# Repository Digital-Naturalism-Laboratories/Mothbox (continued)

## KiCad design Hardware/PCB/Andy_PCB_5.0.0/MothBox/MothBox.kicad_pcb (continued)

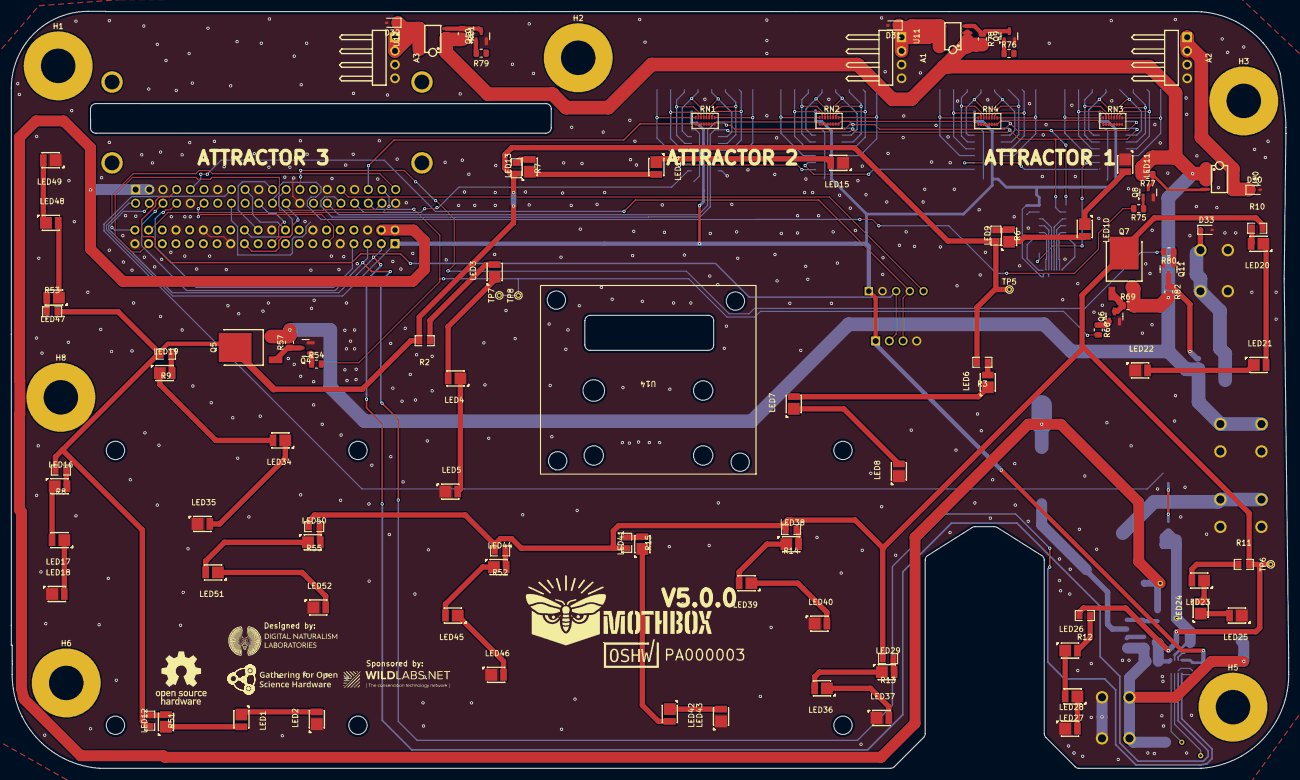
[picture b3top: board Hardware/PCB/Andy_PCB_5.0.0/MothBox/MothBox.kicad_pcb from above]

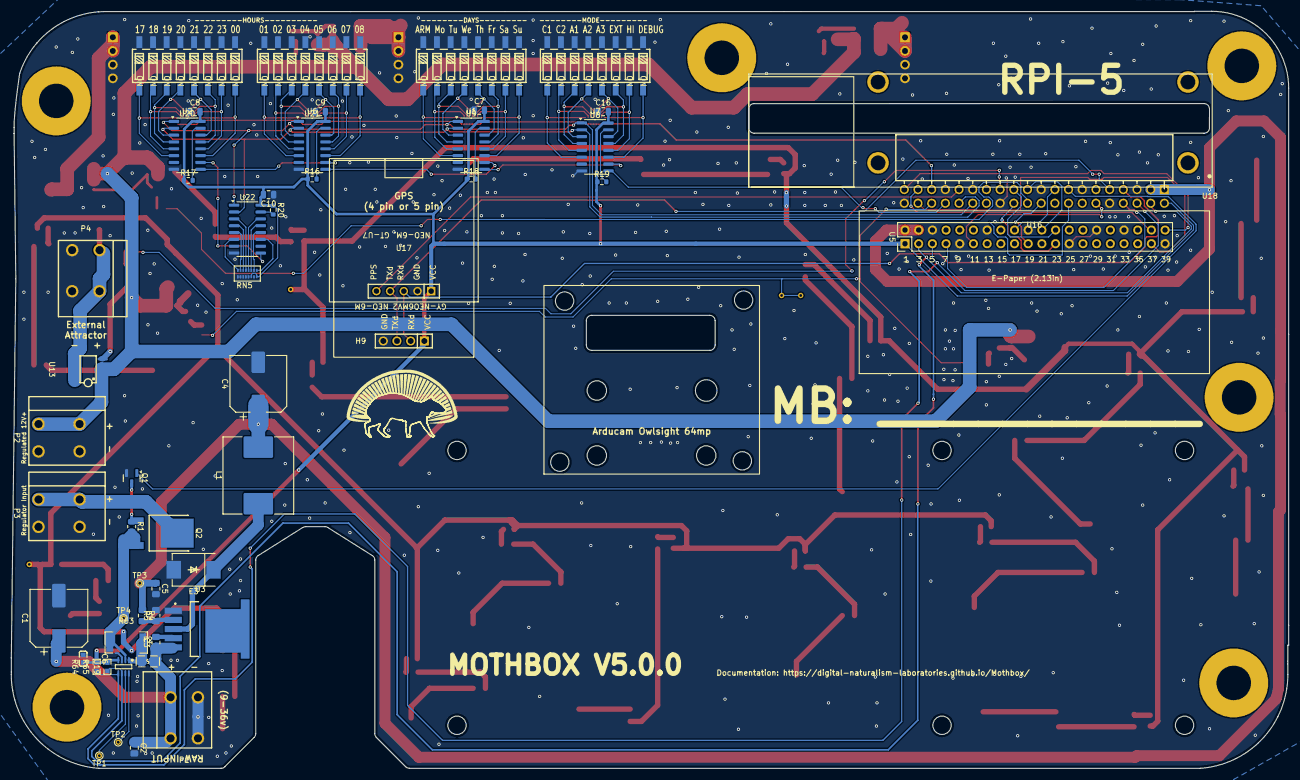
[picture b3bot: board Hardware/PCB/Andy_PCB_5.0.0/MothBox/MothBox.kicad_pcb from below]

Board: 2 copper layers, 237.0 x 140.5 mm, 163 parts (54 on the bottom side), 152 nets.

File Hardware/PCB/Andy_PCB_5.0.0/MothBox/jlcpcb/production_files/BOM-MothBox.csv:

Comment,Designator,Footprint,LCSC,Quantity
3.3K,R5,C_0805_2012Metric_Pad1.18x1.45mm_HandSolder,C114531,1
SUD50P06-15-GE3,"Q2,Q5,Q7",TO-252-3_L6.5-W5.8-P4.58-BL,C141584,3
0.1µF,C6,C0603,C14663,1
Polyfuse,F2,F0805,C22435897,1
0.1/1% (PT2512FK-070R1L),R63,R2512,C23067426,1
FDS4435BZ,"U10,U11,U12,U13",SOIC-8_L5.0-W4.0-P1.27-LS6.0-BL,C23931,4
330uF 50V,C4,CP_Elec_10x10,C2687701,1
GPS 4 pin 2.54-1*4P母,H9,GPS4pin_HDR-TH_4P-P2.54-V-F,C2718488,1
XL-2835UWC-02,"LED1,LED10,LED11,LED12,LED13,LED14,LED15,LED16,LED17,LED18,LED19,LED2,LED20,LED21,LED22,LED23,LED24,LED25,LED26,LED27,LED28,LED29,LED3,LED34,LED35,LED36,LED37,LED38,LED39,LED4,LED40,LED41,LED42,LED43,LED44,LED45,LED46,LED47,LED48,LED49,LED5,LED50,LED51,LED52,LED6,LED7,LED8,LED9",LED-SMD_L3.5-W2.8-RD_1.25T-2PWT,C2843876,48
Female Inv Socket Pi 2.54-2*20,U16,HDR-TH_40P-P2.54-H-F-R2-C20-W8.5,C2897440,1
Raw Input,"P1,P2,P3,P4",CONN-TH_2P-P5.08_DIBO_DB142R-5.08-2P,C2898709,4
FRC0805F30R0TS,"R10,R11,R12,R13,R14,R15,R51,R52,R53,R6,R7,R8,R9",R0805,C2907256,13
10k,"R64,R65",R0603,C2930027,2
FRC0805F30R0TS,"R2,R3,R55",R0805,C2934094,3
0.1uF 50V,"C2,C3,C5",C_0805_2012Metric_Pad1.18x1.45mm_HandSolder,C2976900,3
BC817,"Q1,Q10,Q11,Q4,Q6,Q8,Q9",SOT-23,C39828,7
ESD12VD3B-TP,"D30,D31,D32,D33",D_SOD-323,C435886,4
PZ254R-11-04P,"A1,A2,A3",HDR-TH_4P-P2.54-H-M-W10.4,C492412,3
CD74HC4067M96E4,"U8,U9",SOIC-24_L15.4-W7.5-P1.27-LS10.3-BL,C496123,2
0.1uF,"C16,C17",C_0805_2012Metric,C49678,2
5A 47uH,L1,L_Chilisin_BMRG00131360,C497913,1
GPs 5 pin PM2.54-1*5,U17,GPS5pin_HDR-TH_5P-P2.54-V-F,C5116488,1
XL4015E1,U3,TO-263-5_L10.2-W8.9-P1.70-TL,C51661,1
RASPBERRY_PI_5,U5,EPAPER_PinHeader_2x20_P2.54mm_Vertical,C5224014,1
Days,"U1,U2,U6,U7",SW-SMD_SMXS-08K-TP,C5439767,4
SK54C,E3,SMC_L6.9-W5.9-LS8.0-RD,C5449119,1
10k,"R1,R4,R57,R69,R77,R78,R81,R82",R_0805_2012Metric,C84376,8
INA219BIDCNT,U19,SOT-23-8_L3.0-W1.7-P0.65-LS2.8-BR,C87469,1
470uF 50V,C1,CP_Elec_10x12.5,C90272,1
1k,"R54,R66,R75,R76,R79,R80",R_0805_2012Metric,C95781,6
RASPBERRY_PI_4B_4GB,U18,MODULE_RASPBERRY_PI_4B_4GB_Sideways,,1
~,B1,Talentcell,,1

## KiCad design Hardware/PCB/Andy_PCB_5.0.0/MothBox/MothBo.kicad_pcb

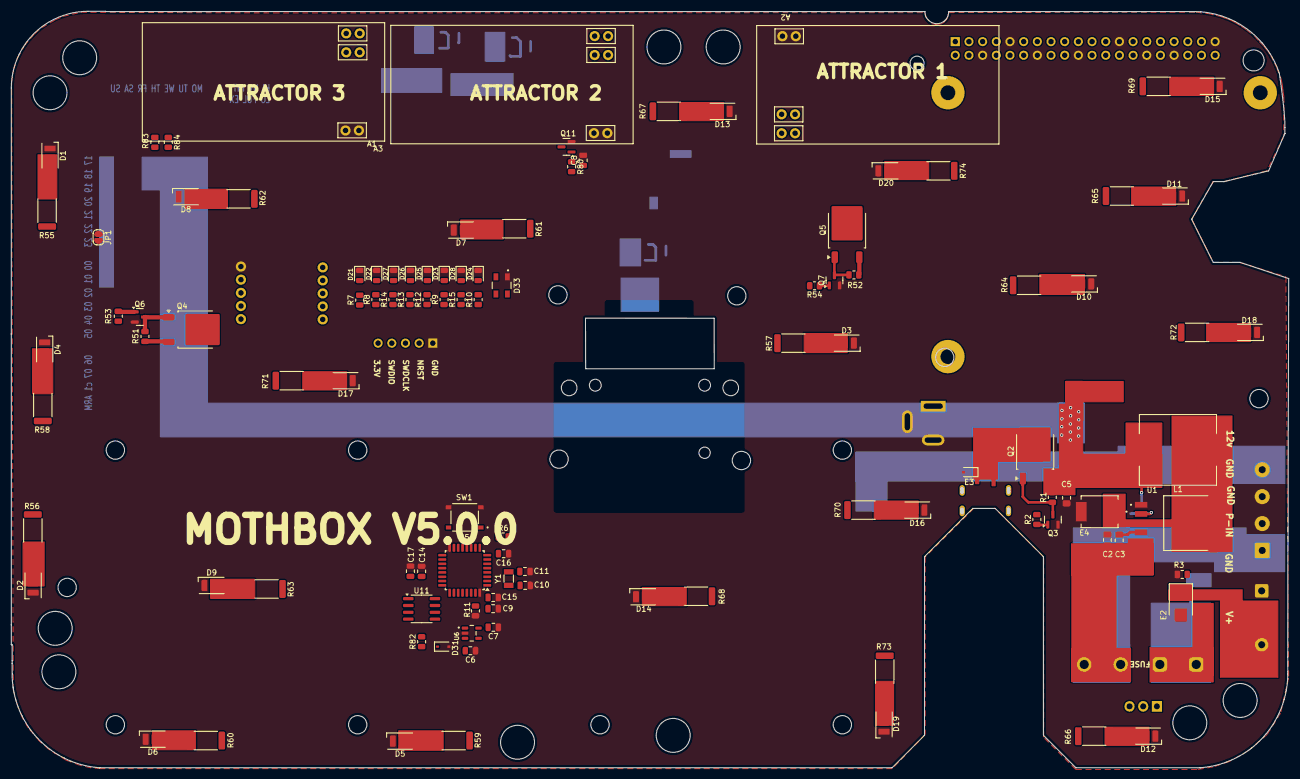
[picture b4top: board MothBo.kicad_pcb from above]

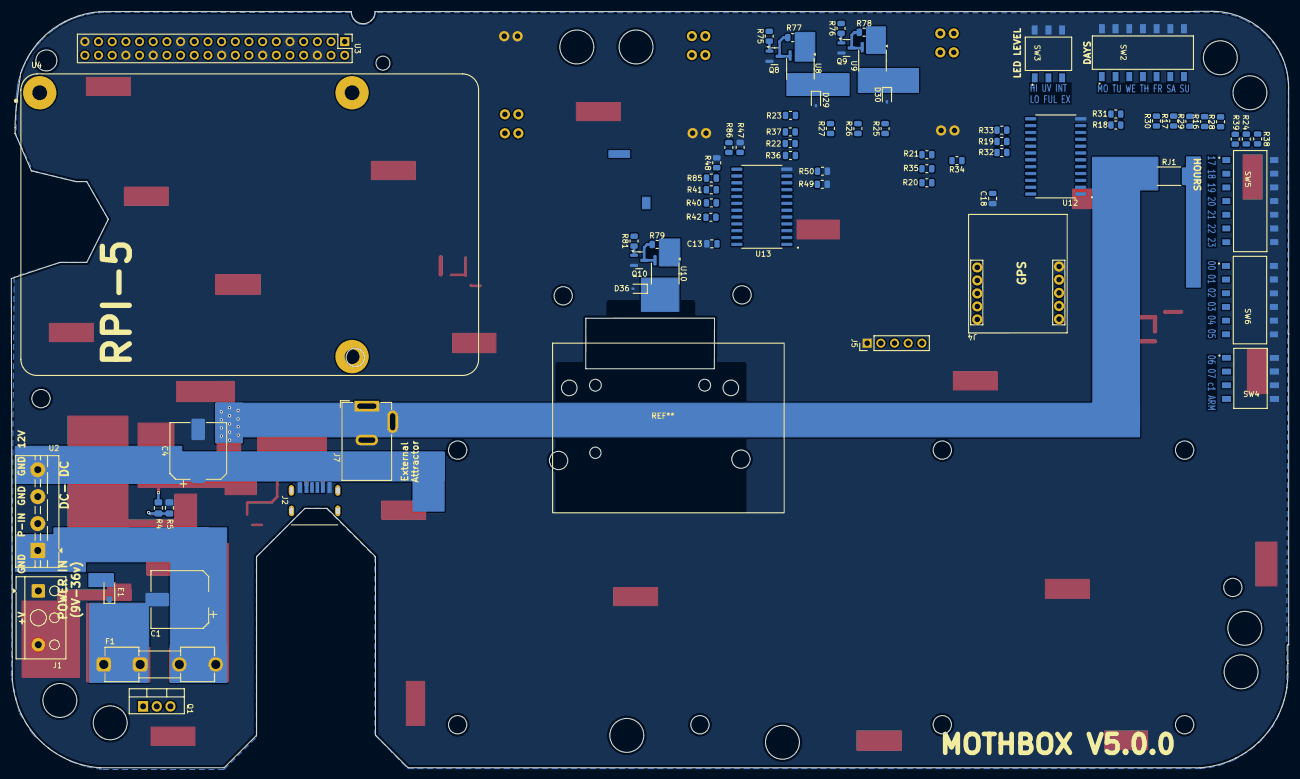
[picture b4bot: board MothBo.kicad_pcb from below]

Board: 2 copper layers, 237.2 x 140.5 mm, 178 parts (73 on the bottom side), 119 nets.

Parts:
A1, A2, A3: Attractor; attractor
C1: 470uF 50V; CP_Elec_10x12.5
C2, C3, C5: 0.1uF 50V; C_0805_2012Metric_Pad1.18x1.45mm_HandSolder
C4: 330uF 50V; CP_Elec_10x10
C6, C7, C17: 1uF; C_0805_2012Metric
C8: 100nF; C_0805_2012Metric
C9, C13, C14, C15, C16, C18: 0.1uF; C_0805_2012Metric
C10, C11: 12pF; C_0805_2012Metric
D1, D2, D3, D4, D5, D6, D7, D8, D9, D10, D11, D12, D13, D14, D15, D16, D17, D18, D19, D20: LED; LED_Everlight-SMD3528_3.5x2.8mm_67-21ST
D21, D22, D23, D24, D25, D26, D27, D28: LED; LED_0805_2012Metric
D29, D30, D31, D36: ESD12VD3B-TP; D_SOD-323
D33: IN-PI33TBTPRPGPB; LED_IN-PI33TBTPRPGPB
E1: BZT52Bxx; D_SOD-123F
E2: SMBJ36A; D_SMB
E3: ESD5V0D3B; D_SOD-323
E4: SK54C; DIO_SK54C
F1: 7A Fuse; Fuseholder_Clip-5x20mm_Eaton_1A5601-01_Inline_P20.80x6.76mm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
J1: Screw_Terminal_01x02; TerminalBlock_RND_205-00023_1x02_P10.00mm_Horizontal
J2: TYPE-C-31-M-17; TYPEC31M17
J4: GPS Header; Untitled
J5: Conn_01x05_Pin; PinHeader_1x05_P2.54mm_Vertical
J7: DC Power Jack; BarrelJack_GCT_DCJ200-10-A_Horizontal
JP1: SolderJumper_2_Open; SolderJumper-2_P1.3mm_Open_RoundedPad1.0x1.5mm
L1: 5A 47uH; L_Chilisin_BMRG00131360
Q1: IRF9540N; TO-220-3_Vertical
Q2, Q4, Q5: TJ10S04M3L,LXHQ; TO-252-2
Q3, Q6, Q7, Q8, Q9, Q10, Q11: BC817; SOT-23
R1, R3, R16, R17, R18, R19, R20, R21, R22, R23, R24, R25, R26, R27, R28, R29, R30, R31, R32, R33, R34, R35, R36, R37, R38, R39, R40, R41, R42, R51, R52, R77, R78, R79, R82: 10k; R_0805_2012Metric
R2, R7, R8, R9, R10, R12, R13, R14, R15, R53, R54, R75, R76, R80, R81: 1k; R_0805_2012Metric
R4: 10K; C_0805_2012Metric_Pad1.18x1.45mm_HandSolder
R5: 3.3K; C_0805_2012Metric_Pad1.18x1.45mm_HandSolder
R6, R11: 10K; R_0805_2012Metric
R47, R48, R49, R50, R83, R84, R85, R86: DNP; R_0805_2012Metric
R55, R56, R57, R58, R59, R60, R61, R62, R63, R64, R65, R66, R67, R68, R69, R70, R71, R72, R73, R74: 170R; R_2512_6332Metric
RJ1: 0R; R_2512_6332Metric
SW1: SW_Push; SW_TS-1187A-B-A-B
SW2: Days; SW_DS04-254-2-07BK-SMT
SW3: Power; SW_DS04-254-2-03BK-SMT
SW4: seq tog; SW_DS04-254-2-04BK-SMT
SW5: Hours; SW_DS04-254-2-07BK-SMT
SW6: Hours; SW_DS04-254-2-06BK-SMT
U1: XL4015; CONV_XL4015
U2: 9V-36V to 12V 5A 60W; TerminalBlock_MaiXu_MX126-5.0-04P_1x04_P5.00mm
U3: RASPBERRY_PI_5; PinHeader_2x20_P2.54mm_Vertical
U4: RASPBERRY_PI_4B_4GB; MODULE_RASPBERRY_PI_4B_4GB
U5: STM32L031K6Tx; LQFP-32_7x7mm_P0.8mm
U6: TLV75733PDBVR; SOT95P280X145-5N
U8, U9, U10, U11: IRF9335TRPBF; SOIC-8_3.9x4.9mm_P1.27mm
U12, U13: CD74HC4067M96E4; SOIC127P1030X265-24N
Y1: 32.768kHz; Crystal_SMD_3215-2Pin_3.2x1.5mm

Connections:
+3.3V: C7.2, C9.2, C13.2, C14.2, C15.2, C16.2, C17.2, C18.2, D33.3 (VDD), J4.VCC, J5.5, R6.1, R16.1, R17.1, R18.1, R19.1, R20.1, R21.1, R22.1, R23.1, R24.1, R25.1, R26.1, R27.1, R28.1, R29.1, R30.1, R31.1, R32.1, R33.1, R34.1, R35.1, R36.1, R37.1, R38.1, R39.1, R40.1, R41.1, R42.1, R83.1, R84.1, R85.1, R86.1, U3.1 (3V3), U3.17 (3V3), U5.1 (VDD), U5.5 (VDDA), U5.17 (VDD), U6.5 (OUT), U12.24 (VCC), U13.24 (VCC)
+5V: C4.1, C5.1, C6.2, L1.2, Q2.3 (S), R1.2, R4.1, RJ1.1, U6.1 (IN), U6.3 (EN)
+12V: Q4.3 (S), Q5.3 (S), R51.2, R52.2, R77.2, R78.2, R79.2, R82.2, U2.4 (Vout+), U8.1 (S), U8.2 (S), U8.3 (S), U9.1 (S), U9.2 (S), U9.3 (S), U10.1 (S), U10.2 (S), U10.3 (S), U11.1 (S), U11.2 (S), U11.3 (S)
/GPS+Switches/Armed/Disarmed: R21.2, SW4.1A, U12.23 (I8)
/GPS+Switches/Fri: R30.2, SW2.3A, U12.4 (I5)
/GPS+Switches/Hour_1: R36.2, SW5.7A, U13.9 (I0)
/GPS+Switches/Hour_2: R22.2, SW5.6A, U13.8 (I1)
/GPS+Switches/Hour_3: R37.2, SW5.5A, U13.7 (I2)
/GPS+Switches/Hour_4: R23.2, SW5.4A, U13.6 (I3)
/GPS+Switches/Hour_5: R38.2, SW5.3A, U13.5 (I4)
/GPS+Switches/Hour_6: R24.2, SW5.2A, U13.4 (I5)
/GPS+Switches/Hour_7: R39.2, SW5.1A, U13.3 (I6)
/GPS+Switches/Hour_8: R40.2, SW6.6A, U13.18 (I13)
/GPS+Switches/Hour_9: R25.2, SW6.5A, U13.17 (I14)
/GPS+Switches/Hour_10: R41.2, SW6.4A, U13.16 (I15)
/GPS+Switches/Hour_11: R26.2, SW6.3A, U13.19 (I12)
/GPS+Switches/Hour_12: R42.2, SW6.2A, U13.20 (I11)
/GPS+Switches/Hour_13: R27.2, SW6.1A, U13.21 (I10)
/GPS+Switches/Max_PW: R33.2, SW3.1A, U12.16 (I15)
/GPS+Switches/Med_PW: R19.2, SW3.2A, U12.17 (I14)
/GPS+Switches/Min_PW: R32.2, SW3.3A, U12.18 (I13)
/GPS+Switches/Mon: R28.2, SW2.7A, U12.7 (I2)
/GPS+Switches/Sat: R18.2, SW2.2A, U12.5 (I4)
/GPS+Switches/Seq_1: R34.2, SW4.4A, U12.20 (I11)
/GPS+Switches/Seq_2: R20.2, SW4.3A, U12.21 (I10)
/GPS+Switches/Seq_3: R35.2, SW4.2A, U12.22 (I9)
/GPS+Switches/Sun: R31.2, SW2.1A, U12.6 (I3)
/GPS+Switches/Thur: R17.2, SW2.4A, U12.3 (I6)
/GPS+Switches/Tue: R16.2, SW2.6A, U12.8 (I1)
/GPS+Switches/Wed: R29.2, SW2.5A, U12.9 (I0)
/Photo LED's/+12V_L_LED: Q4.1 (D), R55.1, R56.1, R57.1, R58.1, R59.1, R60.1, R61.1, R62.1, R63.1, R64.1
/Photo LED's/+12V_R_LED: Q5.1 (D), R65.1, R66.1, R67.1, R68.1, R69.1, R70.1, R71.1, R72.1, R73.1, R74.1
/Power/FB: R4.2, R5.1, U1.2 (FB)
/Power/PWR_IN: C1.1, C2.1, C3.1, F1.2, U1.5 (VIN), U2.1 (Vin+)
/Power/VBUS: E3.1 (K), J2.A9 (VBUS_1), J2.B9 (VBUS_2), Q2.1 (D)
/RPI5+MCU/BOOT0: R11.1, U5.31 (BOOT0)
/RPI5+MCU/NRST: C8.1, J5.2, R6.2, SW1.A, SW1.B, U5.4 (NRST)
/RPI5+MCU/OSC_IN: C10.2, U5.2 (PC14), Y1.2
/RPI5+MCU/OSC_OUT: C11.2, U5.3 (PC15), Y1.1
/RPI5+MCU/PA2: R9.1, U5.8 (PA2)
/RPI5+MCU/PA3: R10.1, U5.9 (PA3)
/RPI5+MCU/PA4: R12.1, U5.10 (PA4)
/RPI5+MCU/PA5: R13.1, U5.11 (PA5)
/RPI5+MCU/PA6: R14.1, U5.12 (PA6)
/RPI5+MCU/PA7: R15.1, U5.13 (PA7)
/RPI5+MCU/PA8: R7.1, U5.18 (PA8)
/RPI5+MCU/PA11: R8.1, U5.21 (PA11)
/RPI5+MCU/PA12: D33.2 (DIN), U5.22 (PA12)
/RPI5+MCU/STM_RX: U3.10 (GPIO15/RXD0), U5.19 (PA9)
/RPI5+MCU/STM_TX: U3.8 (GPIO14/TXD0), U5.20 (PA10)
/RPI5+MCU/SWDCLK: J5.3, U5.24 (PA14)
/RPI5+MCU/SWDIO: J5.4, U5.23 (PA13)
/RPI5+MCU/Save for eink: U3.11 (GPIO17/GPIO_GEN0), U3.18 (GPIO24/GPIO_GEN5), U3.19 (GPIO10/SPI_MOSI), U3.22 (GPIO25/GPIO_GEN6), U3.23 (GPIO11/SPI_SCLK), U3.24 (GPIO8/~SPI_CE0)
/UV LED PCB/+12V_PCB1: A2.3 (VCC), A2.4 (VCC), D29.1 (K), U8.5 (D), U8.6 (D), U8.7 (D), U8.8 (D)
/UV LED PCB/+12V_PCB2: A1.3 (VCC), A1.4 (VCC), D31.1 (K), U11.5 (D), U11.6 (D), U11.7 (D), U11.8 (D)
/UV LED PCB/+12V_PCB3: A3.3 (VCC), A3.4 (VCC), D30.1 (K), U9.5 (D), U9.6 (D), U9.7 (D), U9.8 (D)
/UV LED PCB/+12V_PCB4: D36.1 (K), J7.1, U10.5 (D), U10.6 (D), U10.7 (D), U10.8 (D)
COM_I/O: U3.36 (GPIO16), U12.1 (COM_I/O), U13.1 (COM_I/O)
EN_MUX1: JP1.1 (A), U3.16 (GPIO23/GPIO_GEN4), U12.15 (~E)
EN_MUX2: JP1.2 (B), U3.29 (GPIO5), U13.15 (~E)
GND: A1.5 (GND), A1.6 (GND), A2.5 (GND), A2.6 (GND), A3.5 (GND), A3.6 (GND), C1.2, C2.2, C4.2, C5.2, C6.1, C7.1, C8.2, C9.1, C10.1, C11.1, C13.1, C14.1, C15.1, C16.1, C17.1, C18.1, D1.1 (K), D2.1 (K), D3.1 (K), D4.1 (K), D5.1 (K), D6.1 (K), D7.1 (K), D8.1 (K), D9.1 (K), D10.1 (K), D11.1 (K), D12.1 (K), D13.1 (K), D14.1 (K), D15.1 (K), D16.1 (K), D17.1 (K), D18.1 (K), D19.1 (K), D20.1 (K), D21.1 (K), D22.1 (K), D23.1 (K), D24.1 (K), D25.1 (K), D26.1 (K), D27.1 (K), D28.1 (K), D29.2 (A), D30.2 (A), D31.2 (A), D33.1 (GND), D36.2 (A), E2.2 (A), E3.2 (A), E4.A, J1.1, J2.A12 (GND_1), J2.B12 (GND_2), J4.GND, J5.1, J7.2, J7.3 (MountPin), Q3.2 (E), Q6.2 (E), Q7.2 (E), Q8.2 (E), Q9.2 (E), Q10.2 (E), Q11.2 (E), R3.1, R5.2, R11.2, R47.2, R48.2, R49.2, R50.2, SW1.C, SW1.D, SW2.1B, SW2.2B, SW2.3B, SW2.4B, SW2.5B, SW2.6B, SW2.7B, SW3.1B, SW3.2B, SW3.3B, SW4.1B, SW4.2B, SW4.3B, SW4.4B, SW5.1B, SW5.2B, SW5.3B, SW5.4B, SW5.5B, SW5.6B, SW5.7B, SW6.1B, SW6.2B, SW6.3B, SW6.4B, SW6.5B, SW6.6B, U1.1 (GND), U2.2 (Vin-), U2.3 (Vout-), U3.6 (GND), U3.9 (GND), U3.14 (GND), U3.20 (GND), U3.25 (GND), U3.30 (GND), U3.34 (GND), U3.39 (GND), U5.16 (VSS), U5.32 (VSS), U6.2 (GND), U12.12 (GND), U13.12 (GND)
GPS_SCL: J4.SCL, U3.5 (GPIO3/SCL1)
GPS_SDA: J4.SDA, U3.3 (GPIO2/SDA1)
L_LED_CTRL: R53.2, R54.2, U3.31 (GPIO6)
unnamed: D1.2 (A), R55.2
unnamed: D2.2 (A), R56.2
unnamed: D3.2 (A), R57.2
unnamed: D4.2 (A), R58.2
unnamed: D5.2 (A), R59.2
unnamed: D6.2 (A), R60.2
unnamed: D7.2 (A), R61.2
unnamed: D8.2 (A), R62.2
unnamed: D9.2 (A), R63.2
unnamed: D10.2 (A), R64.2
unnamed: D11.2 (A), R65.2
unnamed: D12.2 (A), R66.2
unnamed: D13.2 (A), R67.2
unnamed: D14.2 (A), R68.2
unnamed: D15.2 (A), R69.2
unnamed: D16.2 (A), R70.2
unnamed: D17.2 (A), R71.2
unnamed: D18.2 (A), R72.2
unnamed: D19.2 (A), R73.2
unnamed: D20.2 (A), R74.2
unnamed: D21.2 (A), R7.2
unnamed: D22.2 (A), R8.2
unnamed: D23.2 (A), R9.2
unnamed: D24.2 (A), R10.2
unnamed: D25.2 (A), R12.2
unnamed: D26.2 (A), R13.2
unnamed: D27.2 (A), R14.2
unnamed: D28.2 (A), R15.2
unnamed: E1.2 (A), Q1.1 (G), R3.2
unnamed: E1.1 (K), F1.1, Q1.3 (S)
unnamed: E2.1 (K), J1.2, Q1.2 (D)
unnamed: E4.C, L1.1, U1.3 (SW), U1.3.1 (SW)
unnamed: Q2.2 (G), Q3.3 (C), R1.1
unnamed: Q3.1 (B), R2.1
unnamed: Q4.2 (G), Q6.3 (C), R51.1
unnamed: Q5.2 (G), Q7.3 (C), R52.1
unnamed: Q6.1 (B), R53.1
unnamed: Q7.1 (B), R54.1
unnamed: Q8.1 (B), R75.1
unnamed: Q8.3 (C), R77.1, U8.4 (G)
unnamed: Q9.1 (B), R76.1
unnamed: Q9.3 (C), R78.1, U9.4 (G)
unnamed: Q10.1 (B), R81.1
unnamed: Q10.3 (C), R79.1, U10.4 (G)
unnamed: Q11.1 (B), R80.1
unnamed: Q11.3 (C), R82.1, U11.4 (G)
unnamed: RJ1.2, U3.2 (5V), U3.4 (5V)
unnamed: C3.2, U1.4 (VC)
RPI_CTRL: R2.2, U3.35 (GPIO19)
S0_MUX: R50.1, R83.2, U3.33 (GPIO13), U12.10 (S0), U13.10 (S0)
S1_MUX: R49.1, R84.2, U3.13 (GPIO27/GPIO_GEN2), U12.11 (S1), U13.11 (S1)
S2_MUX: R48.1, R85.2, U3.12 (GPIO18/GPIO_GEN1), U12.14 (S2), U13.14 (S2)
S3_MUX: R47.1, R86.2, U3.15 (GPIO22/GPIO_GEN3), U12.13 (S3), U13.13 (S3)
UV1_CTRL: R75.2, R76.2, R80.2, U3.21 (GPIO9/SPI_MISO)
UV4_EX_CTRL: R81.2, U3.26 (GPIO7/~SPI_CE1)

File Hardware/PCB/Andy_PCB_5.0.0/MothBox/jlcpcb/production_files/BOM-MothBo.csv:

Comment,Designator,Footprint,LCSC,Quantity
3.3K,R5,C_0805_2012Metric_Pad1.18x1.45mm_HandSolder,C114531,1
"TJ10S04M3L,LXHQ","Q2,Q4,Q5",TO-252-2,C115837,3
12pF,"C10,C11",C_0805_2012Metric,C1792,2
Days,"SW2,SW5",SW_DS04-254-2-07BK-SMT,C18198129,2
IRF9335TRPBF,"U10,U11,U8,U9",SOIC-8_3.9x4.9mm_P1.27mm,C23931,4
IRF9540N,Q1,TO-220-3_Vertical,C2575,1
330uF 50V,C4,CP_Elec_10x10,C2687701,1
1uF,"C17,C6,C7",C_0805_2012Metric,C28323,3
TYPE-C-31-M-17,J2,TYPEC31M17,C283540,1
SMBJ36A,E2,D_SMB,C2848704,1
170R,"R55,R56,R57,R58,R59,R60,R61,R62,R63,R64,R65,R66,R67,R68,R69,R70,R71,R72,R73,R74,RJ1",R_2512_6332Metric,C2934094,21
0.1uF 50V,"C2,C3,C5",C_0805_2012Metric_Pad1.18x1.45mm_HandSolder,C2976900,3
SW_Push,SW1,SW_TS-1187A-B-A-B,C318884,1
Sequence+Toggle,SW4,SW_DS04-254-2-04BK-SMT,C319038,1
Power,SW3,SW_DS04-254-2-03BK-SMT,C319040,1
DC Power Jack,J7,BarrelJack_GCT_DCJ200-10-A_Horizontal,C319099,1
BZT52Bxx,E1,D_SOD-123F,C362312,1
LED,"D1,D10,D11,D12,D13,D14,D15,D16,D17,D18,D19,D2,D20,D3,D4,D5,D6,D7,D8,D9",LED_Everlight-SMD3528_3.5x2.8mm_67-21ST,C385305,20
BC817,"Q10,Q11,Q3,Q6,Q7,Q8,Q9",SOT-23,C39828,7
9V-36V to 12V 5A 60W,U2,TerminalBlock_MaiXu_MX126-5.0-04P_1x04_P5.00mm,C424682,1
ESD12VD3B-TP,"D29,D30,D31,D36",D_SOD-323,C435886,4
ESD5V0D3B,E3,D_SOD-323,C484322,1
TLV75733PDBVR,U6,SOT95P280X145-5N,C485517,1
CD74HC4067M96E4,"U12,U13",SOIC127P1030X265-24N,C496123,2
Attractor,"A1,A2,A3",attractor,C49661,3
0.1uF,"C13,C14,C15,C16,C18,C8,C9",C_0805_2012Metric,C49678,7
5A 47uH,L1,L_Chilisin_BMRG00131360,C497913,1
XL4015,U1,CONV_XL4015,C51661,1
Screw_Terminal_01x02,J1,TerminalBlock_RND_205-00023_1x02_P10.00mm_Horizontal,C5168775,1
IN-PI33TBTPRPGPB,D33,LED_IN-PI33TBTPRPGPB,C527089,1
7A Fuse,F1,Fuseholder_Clip-5x20mm_Eaton_1A5601-01_Inline_P20.80x6.76mm_D1.70mm_Horizontal,C5381734,1
SK54C,E4,DIO_SK54C,C5449119,1
LED,"D21,D22,D23,D24,D25,D26,D27,D28",LED_0805_2012Metric,C5875740,8
GPS Header,"J4,J5",Untitled,C6332198,2
10k,"R1,R11,R16,R17,R18,R19,R20,R21,R22,R23,R24,R25,R26,R27,R28,R29,R3,R30,R31,R32,R33,R34,R35,R36,R37,R38,R39,R4,R40,R41,R42,R51,R52,R6,R77,R78,R79,R82",R_0805_2012Metric,C84376,38
Hours,SW6,SW_DS04-254-2-06BK-SMT,C880354,1
470uF 50V,C1,CP_Elec_10x12.5,C90272,1
STM32L031K6Tx,U5,LQFP-32_7x7mm_P0.8mm,C94085,1
1k,"R10,R12,R13,R14,R15,R2,R53,R54,R7,R75,R76,R8,R80,R81,R9",R_0805_2012Metric,C95781,15
32.768kHz,Y1,Crystal_SMD_3215-2Pin_3.2x1.5mm,C99010,1
DNP,,R_0805_2012Metric,,0
DNP,,R_0805_2012Metric,,0
DNP,,R_0805_2012Metric,,0
DNP,,R_0805_2012Metric,,0
DNP,,R_0805_2012Metric,,0
DNP,,R_0805_2012Metric,,0
DNP,,R_0805_2012Metric,,0
DNP,,R_0805_2012Metric,,0

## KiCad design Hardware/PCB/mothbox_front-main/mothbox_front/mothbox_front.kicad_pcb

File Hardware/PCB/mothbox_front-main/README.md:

# mothbox_front

Design a mainboard for the MothBox

# TODO
Todo list mostly built off the [list of upcoming features for the Mothbox](https://digital-naturalism-laboratories.github.io/Mothbox/docs/about/upcoming/).

## Circuit Designs

### Photo LEDs (Point person Moritz)
These are the white, distributed LEDs that evenly light up the target area for even photography.

- place 12V UV-light / visible light attractor LED boards
- design white light <--> PI interface
- design led drivers: single constant current driver for UV and Flashlight, Relays to switch between both options, part: LDH-25-350
- place white LEDs and drivers

### Attractor LEDs (Point person Moritz)
- Design circuitry to toggle high power output to the attractor LED ports

### Power Regulation
Ideally this PCB should be able to accept a range of power. A [common power regulator that costs around $15](https://www.amazon.com/dp/B0B6VK8BPN?ref=ppx_yo2ov_dt_b_fed_asin_title&th=1) takes *9-36v* and regulates this to an even 12V at 5amps. It would be nice if we could build this into the board, though it could optionally be purchased as is and the board just made to use 12V.

- Design regulator circuit
- design connector (ideally standard barrel jack connector, or pair of + and - plugs)

### Power Management
- Integrated power monitoring (e.g. integrate something like the Adafruit 4226 INA260)
- Display Charge State

### Physical Programming Interface
The scientists often have a hard time programming features of the Mothbox. If possible, as many of these variables a user needs to set should be available as some kind of physical switch or toggle. 

Ideally these switches should be "soft switches" that just change a state on a pin the Pi can read and the internal software can perform the necessary functions. There are likely too many variables to route each pin to a different GPIO pin on the Pi, so a multiplexer is likely warranted to combine these inputs into just a couple GPIO pins for the Pi to read.

- Multiplexer to route the pin states
- Programming Pins
    - Mothbox Schedule
        - Days of week to run
        - Hours to start
        - Duration for each capture sequence (optional)
    - Mothbox State
        - Toggle Armed/ Disarmed
    - Attractor LED TYPE
        - Switch between UV, Visible, or Both
        - Possibly more granular (UV, Blue, Green, White)
    - Attractor LED Power Usage
        - Max Power
        - Medium Power
        - Minimum Power
    - External vs Internal Attractor
        - Toggle between using the internal attractor lights, External port, or both!

### Status indication and feedback
Some sort of low energy method to display this array of possible states, so that in the field one does not have to VNC into the device to know what it is up to. This could be a simple RGB led with color codes that blinks maybe once every couple seconds or something.
- Armed/Disarmed state
- “Is scheduled to run today/within the next 2 hours” indicator
- Copying files
- taking photos
- idle
- sleep / dormant
- error

### Bonus Features
#### GPS
GPS is great primarily because it can give us automatic time syncronization!
Secondarily it is great because it can give us location (but we generally mark GPS and the mothboxes don't move much)
- place GPS antenna / GPS board (mounting holes)
- Or, one could just [buy a GPS hat](https://www.adafruit.com/product/2324)

#### Power Microcontroller
- Integrate low power microcontroller that can fully shut off and wake up the Pi

## Physical Designs and Connections
- place connectors for attractor LED boards
- Place connectors for camera
- Place connectors for 1/4 in bolts that hold the PCB in place in the box (partially done with Andy's latest DXF)

# DONE
- decide on preferred power bank: PB120B1, https://talentcell.com/lithium-ion-battery/24v/pb240b2.html
    - 12V output: 9V-12.6V / 6 A max (direct connection to batteries)
    - 5V, 2.4A

- location and fixation of the power bank

# Order
- Arducam 64 MP
- RPi 5
- Talent Cell battery PB120B1

# Already ordered
- PLANO box

# Wishlist of functionality

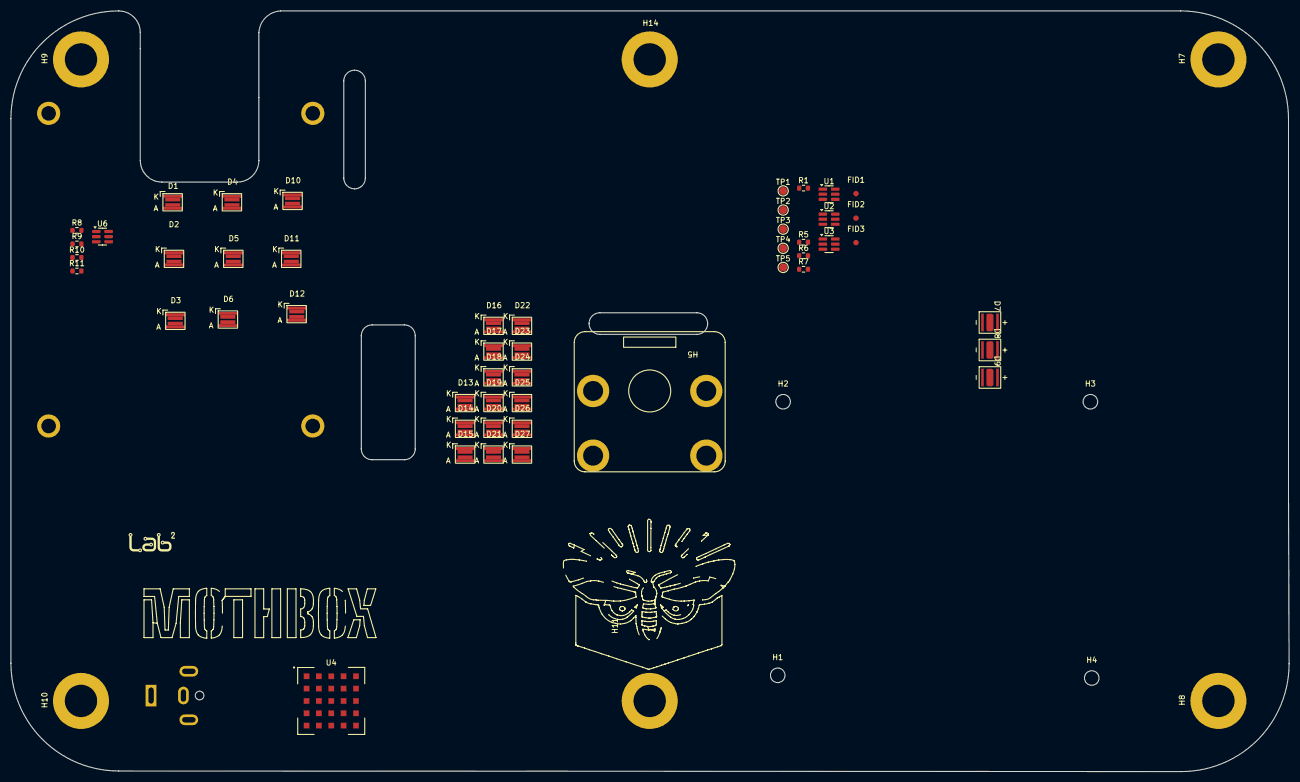
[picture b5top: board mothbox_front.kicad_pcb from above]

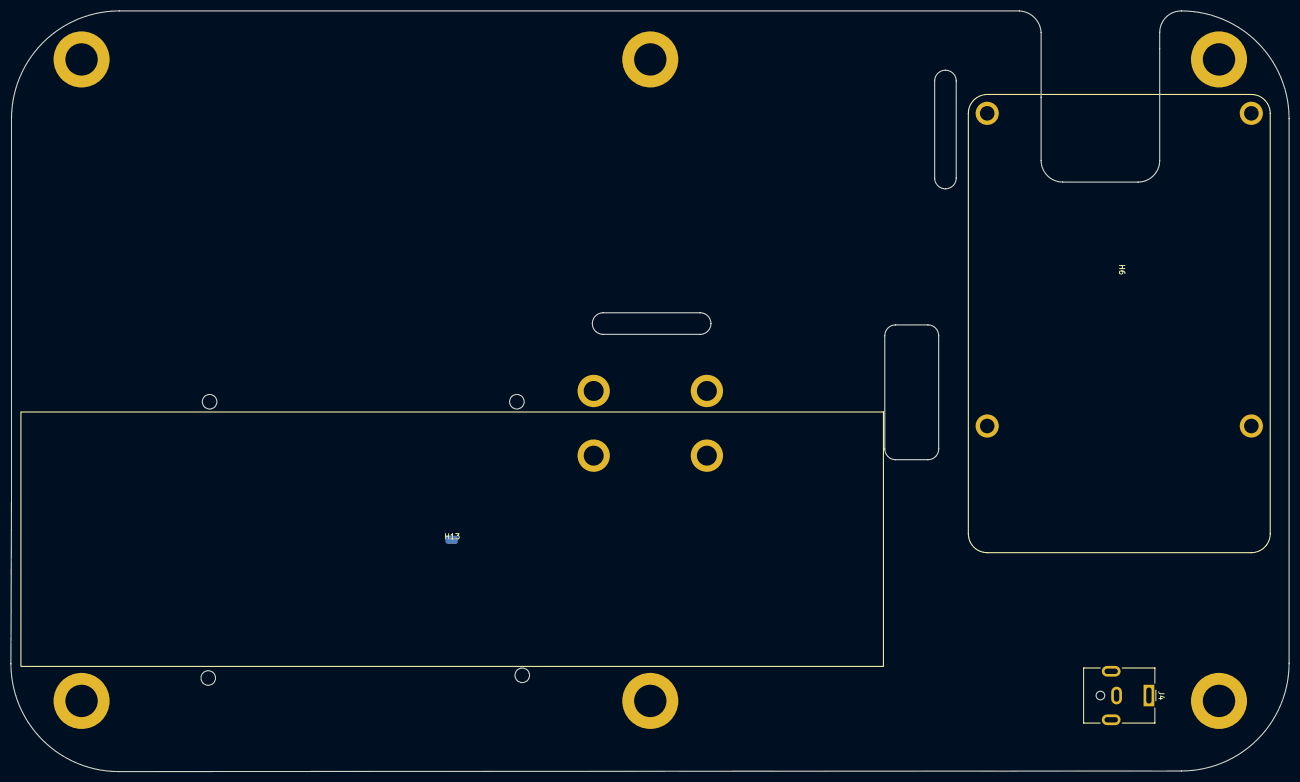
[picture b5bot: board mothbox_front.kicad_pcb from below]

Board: 2 copper layers, 237.1 x 141.1 mm, 63 parts (3 on the bottom side), 23 nets, no tracks yet.

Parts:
D1, D2, D3, D4, D5, D6, D10, D11, D12, D13, D14, D15, D16, D17, D18, D19, D20, D21, D22, D23, D24, D25, D26, D27: LED; LM301_3mm
D7: LED1; Wuerth_HP_Ceramic
D8: LED2; Wuerth_HP_Ceramic
D9: LED3; Wuerth_HP_Ceramic
FID1, FID2, FID3: Fiducial; Fiducial_1mm_Mask3mm
H1, H2, H3, H4: MountingHole_Pad; MountingHole_2.7mm_M2.5_DIN965
H1#2: LabLab Logo; logo_10mm_5mm
H5: Camera; Camera_64MP
H6: PI; RPI_5
H7, H8, H9, H10, H11, H14: Distance; 9774030592R
H13: battery
J4: Barrel_Jack_MountingPin; BarrelJack_CUI_PJ-063AH_Horizontal
R1, R5, R6, R7, R8, R9, R10, R11: 5.1 1/3 W; R_0603_1608Metric
TP1, TP2, TP3, TP4, TP5: LED2+; TestPoint_Pad_D1.5mm
U1, U2, U3, U6: BCR421U; SC-74-6_1.55x2.9mm_P0.95mm
U4: RPMB-3.0BGA-25_5x5_12.19x12.19mm

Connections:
+12V: D1.2 (A), D4.2 (A), D10.2 (A)
/LED+: D7.2 (A), R5.1
/LED-: D9.1 (K), U1.2 (OUT), U1.3 (OUT), U1.5 (OUT), U2.2 (OUT), U2.3 (OUT), U2.5 (OUT), U3.2 (OUT), U3.3 (OUT), U3.5 (OUT)
/T1: D7.3 (PAD), TP3.1
/T2: D8.3 (PAD), TP4.1
/T3: D9.3 (PAD), TP5.1
EN: R5.2, U1.1 (EN)
GND: J4.2, R6.2, R7.2, R11.2, U1.4 (GND), U2.4 (GND), U3.4 (GND), U4.A3 (GND), U4.A4 (GND), U4.B1 (GND), U4.B2 (GND), U4.B3 (GND), U4.B4 (GND), U4.C2 (GND), U4.C3 (GND), U4.C4 (GND), U4.D2 (GND), U4.D3 (GND), U4.D4 (GND), U4.D5 (GND), U4.E3 (GND), U4.E4 (GND), U6.4 (GND)
unnamed: D1.1 (K), D2.2 (A)
unnamed: D2.1 (K), D3.2 (A)
unnamed: D3.1 (K), R8.1
unnamed: D4.1 (K), D5.2 (A)
unnamed: D5.1 (K), D6.2 (A)
unnamed: D6.1 (K), R10.1
unnamed: D7.1 (K), D8.2 (A), TP1.1
unnamed: D8.1 (K), D9.2 (A), TP2.1
unnamed: D12.1 (K), R9.1
unnamed: J4.1, U4.A1 (VIN)
unnamed: R8.2, R9.2, R10.2, U6.2 (OUT), U6.3 (OUT), U6.5 (OUT)
unnamed: R1.1, U1.6 (REXT)
unnamed: R6.1, U2.6 (REXT)
unnamed: R7.1, U3.6 (REXT)
unnamed: R11.1, U6.6 (REXT)

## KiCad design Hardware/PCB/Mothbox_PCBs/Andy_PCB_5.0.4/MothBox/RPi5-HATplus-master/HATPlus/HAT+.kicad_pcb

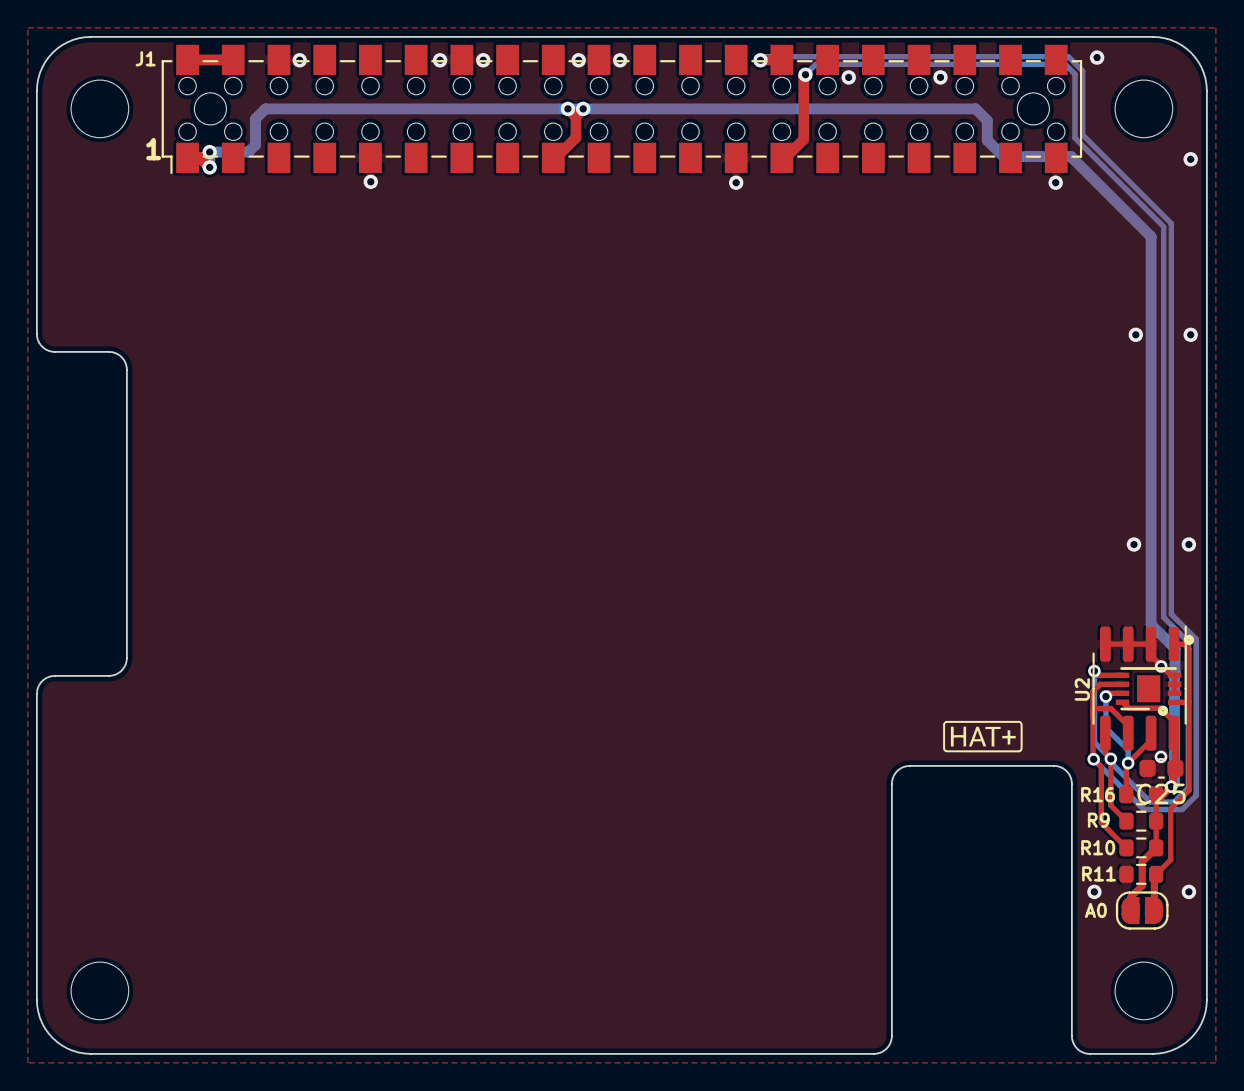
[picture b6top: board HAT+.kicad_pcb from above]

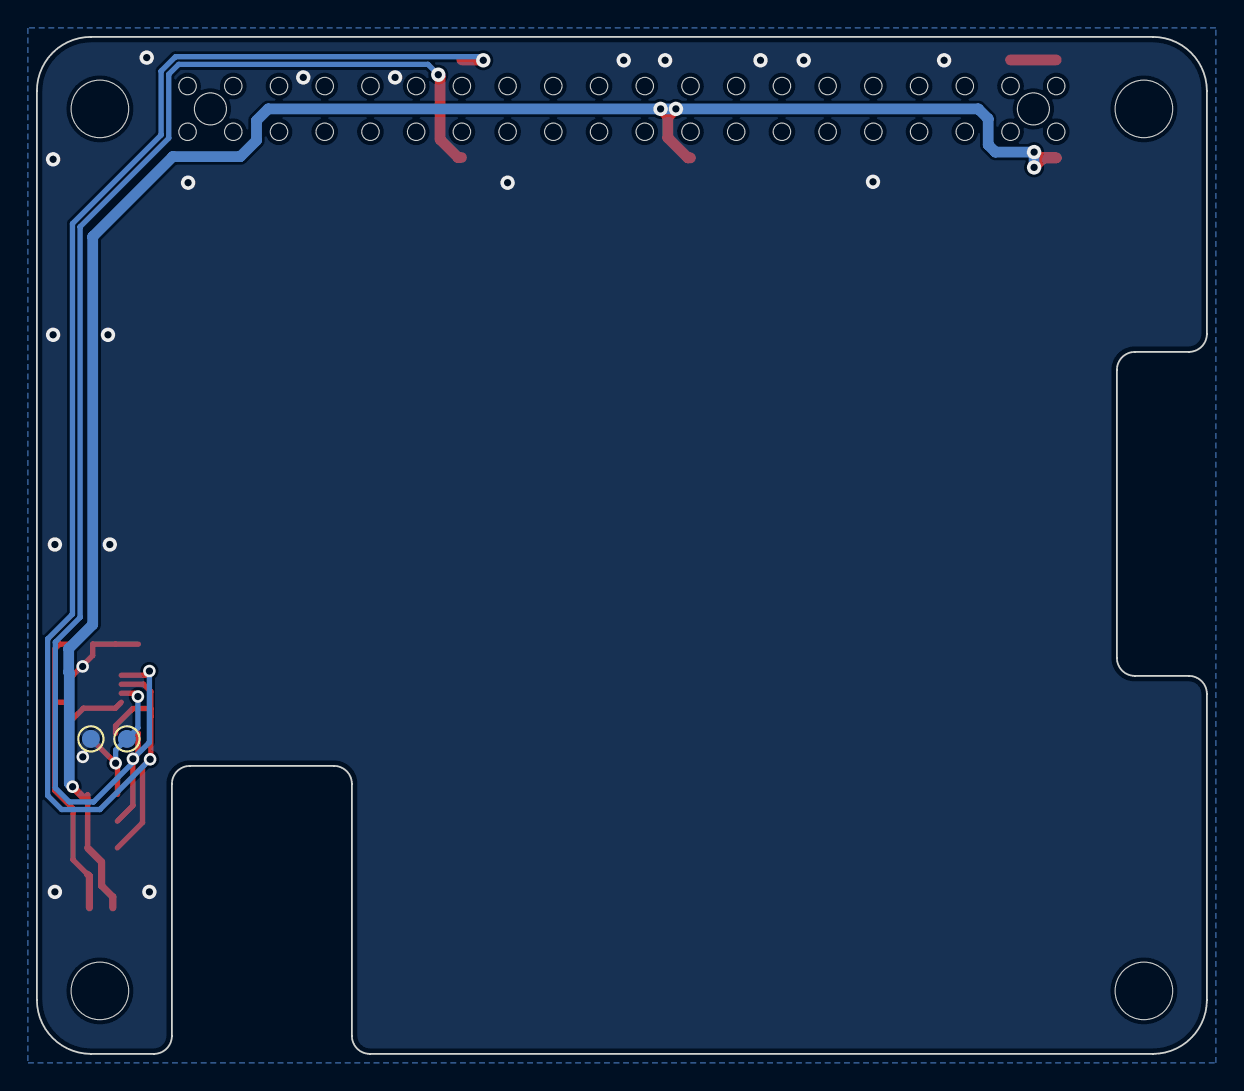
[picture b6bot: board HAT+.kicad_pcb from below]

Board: 4 copper layers, 65.0 x 56.5 mm, 15 parts (2 on the bottom side), 7 nets.

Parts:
A0: SolderJumper_2_Open; SolderJumper-2_P1.3mm_Open_RoundedPad1.0x1.5mm
C25: 100nF; C_0603_1608Metric
GND1: TestPoint_Alt; TestPoint_Pad_D1.0mm
H1, H2, H3, H4: MountingHole 3.2mm; MountingHole_3.2mm_M3_DIN965
J1: Conn_02x20_Odd_Even; Samtec_HLE-120-02-xxx-DV-BE-A_2x20_P2.54mm_Horizontal_Rever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
R9, R10, R11, R16: 3.9k; R_0603_1608Metric
U1: AT24CS64-SSHM; SOIC-8_3.9x4.9mm_P1.27mm
U2: AT24CS64-MAHM; DFN-8-1EP_3x2mm_P0.5mm_EP1.3x1.5mm
WP1: TestPoint_Alt; TestPoint_Pad_D1.0mm

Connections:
/HAT+/HAT_3V3: A0.2 (B), C25.1, J1.1, J1.17, R9.2, R10.2, R16.2, U1.8 (VCC), U2.8 (VCC)
/HAT+/HAT_5V0: J1.2, J1.4
/HAT+/HAT_SCL0: J1.28, R10.1, U1.6 (SCL), U2.6 (SCL)
/HAT+/HAT_SDA0: J1.27, R9.1, U1.5 (SDA), U2.5 (SDA)
GND: C25.2, GND1.1, J1.6, J1.9, J1.14, J1.20, J1.25, J1.30, J1.34, J1.39, R11.1, U1.2 (A1), U1.3 (A2), U1.4 (GND), U2.2 (A1), U2.3 (A2), U2.4 (GND)
unnamed: A0.1 (A), R11.2, U1.1 (A0), U2.1 (A0)
unnamed: R16.1, U1.7 (WP), U2.7 (WP), WP1.1
